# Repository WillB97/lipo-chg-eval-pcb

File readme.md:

# BQ25792/MP2759 LiPo Charger Evaluation Board

[GitHub Pages site](https://willb97.github.io/lipo-chg-eval-pcb/Browse/charger-compare-navigate.html).

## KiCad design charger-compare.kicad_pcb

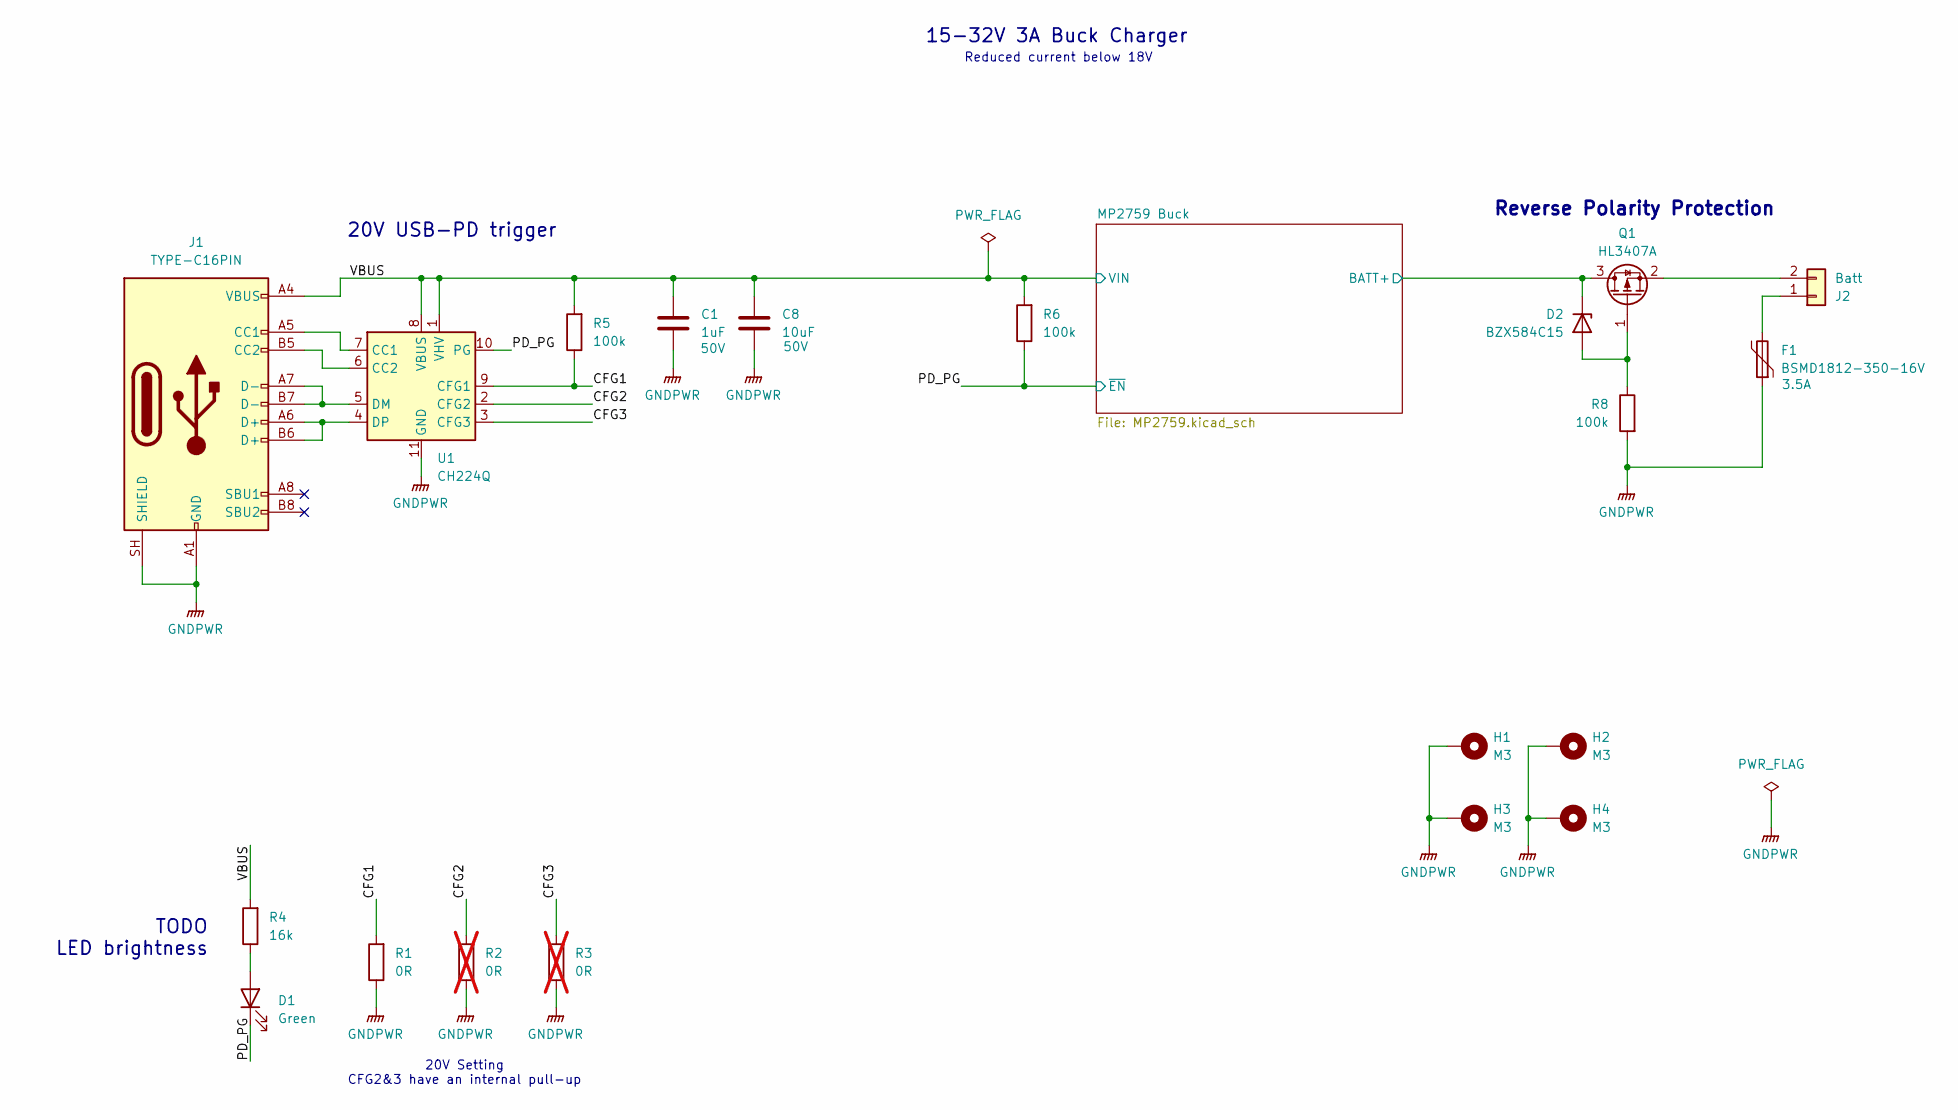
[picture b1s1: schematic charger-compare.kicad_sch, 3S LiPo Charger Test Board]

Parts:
C1: 1uF; C_0603_1608Metric; Voltage 50V; JLC C15849
C8: 10uF; C_0805_2012Metric; Voltage 50V; JLC C440198
D1: Green; LED_0805_2012Metric; JLC C2297
D2: BZX584C15; D_SOD-523; LCSC C19077466
F1: BSMD1812-350-16V; Fuse_1812_4532Metric_Pad1.30x3.40mm_HandSolder; Rating 3.5A; LCSC C5301865
H1, H2, H3, H4: M3; MountingHole_3.2mm_M3_Pad
J1: TYPE-C16PIN; USB_C_Receptacle_Palconn_UTC16-G; LCSC C393939
J2: Batt; AMASS_XT60PW-M_1x02_P7.20mm_Horizontal
Q1: HL3407A; SOT-23; JLC C28646269
R1: 0R; R_0603_1608Metric
R2, R3: 0R; R_0603_1608Metric; not fitted
R4: 16k; R_0402_1005Metric
R5, R6, R8: 100k; R_0402_1005Metric
U1: CH224Q; DFN-10_2x2mm_P0.4mm; LCSC C46061833

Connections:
/CFG1: R1.2, R5.1, U1.9 (CFG1)
/CFG2: R2.2, U1.2 (CFG2)
/CFG3: R3.2, U1.3 (CFG3)
/MP2759 Buck/BATT+: D2.1 (K), Q1.3 (D); also elsewhere on the board
/PD_PG: D1.1 (K), R6.1, U1.10 (PG); also elsewhere on the board
/VBUS: C1.1, C8.1, J1.A4 (VBUS), J1.A9 (VBUS), J1.B4 (VBUS), J1.B9 (VBUS), R4.2, R5.2, R6.2, U1.1 (VHV), U1.8 (VBUS); also elsewhere on the board
GNDPWR: C1.2, C8.2, F1.1, H1.1 (1_1), H2.1 (1_1), H3.1 (1_1), H4.1 (1_1), J1.A1 (GND), J1.A12 (GND), J1.B1 (GND), J1.B12 (GND), J1.SH (SHIELD), R1.1, R2.1, R3.1, R8.2, U1.11 (GND); also elsewhere on the board
unnamed: D1.2 (A), R4.1
unnamed: D2.2 (A), Q1.1 (G), R8.1
unnamed: J1.A5 (CC1), U1.7 (CC1)
unnamed: J1.B5 (CC2), U1.6 (CC2)
unnamed: F1.2, J2.1
unnamed: J2.2, Q1.2 (S)
unnamed: J1.A7 (D-), J1.B7 (D-), U1.5 (DM)
unnamed: J1.A6 (D+), J1.B6 (D+), U1.4 (DP)

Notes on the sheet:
20V USB-PD trigger
Reverse Polarity Protection
TODO LED brightness
20V Setting CFG2&3 have an internal pull-up
Reduced current below 18V
15-32V 3A Buck Charger

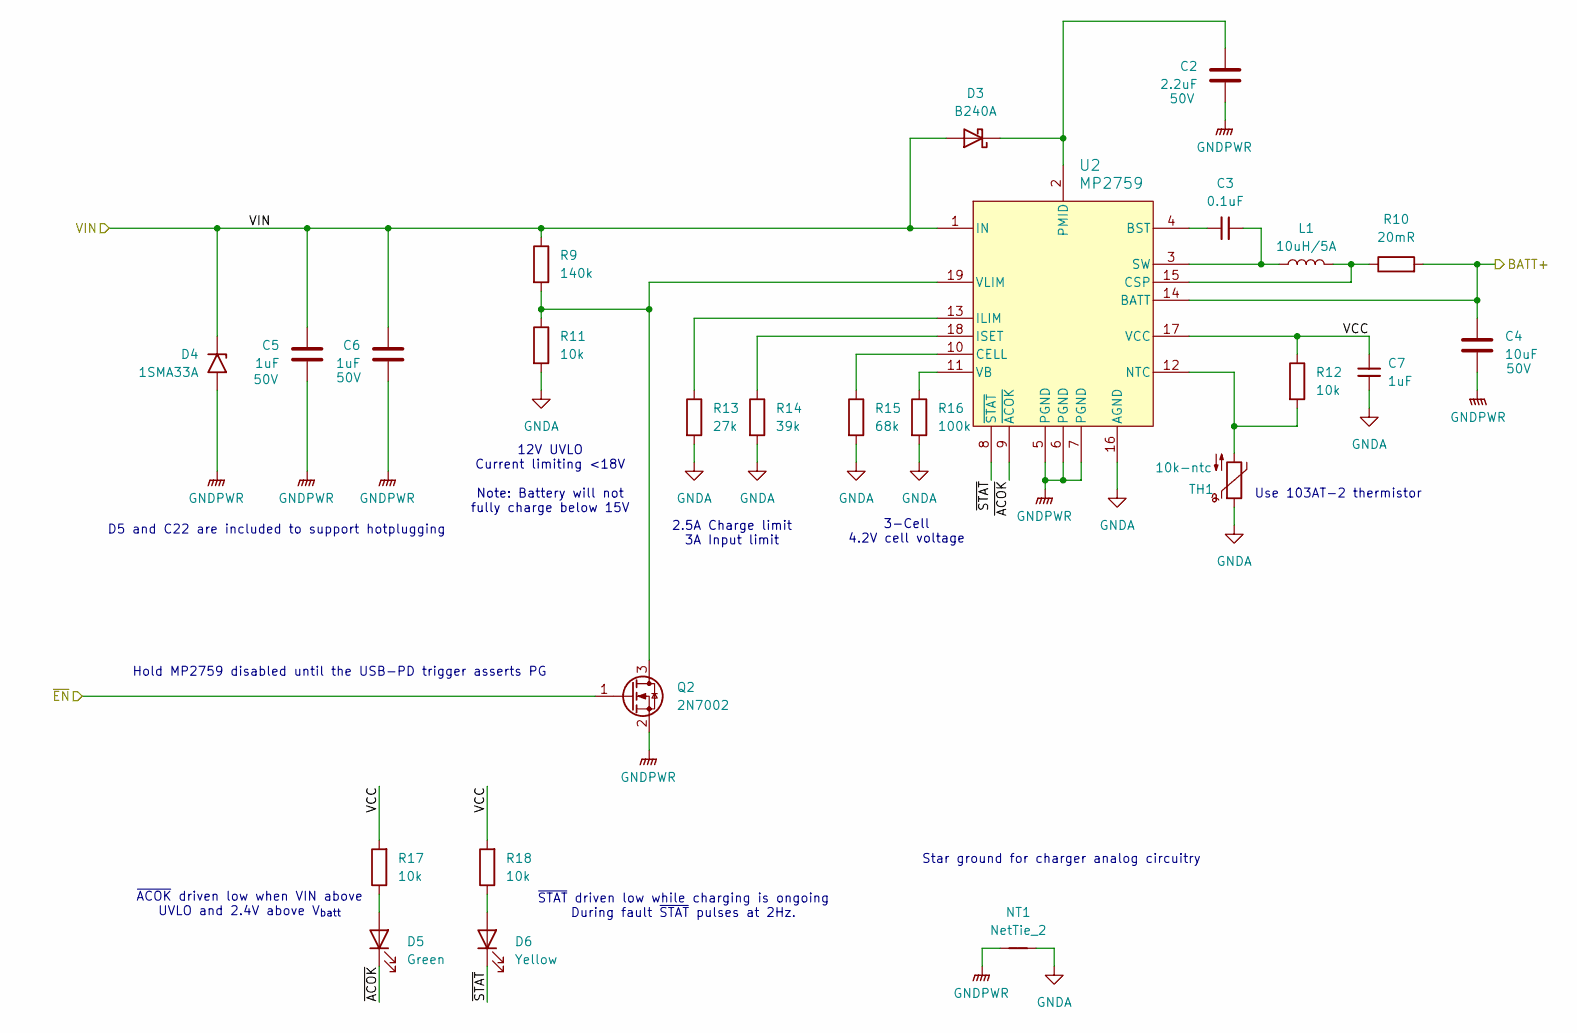
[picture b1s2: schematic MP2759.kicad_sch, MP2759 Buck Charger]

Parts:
C2: 2.2uF; C_0805_2012Metric; Voltage 50V; JLC C377773
C3: 0.1uF; C_0402_1005Metric; Voltage 10V; JLC C307331
C4: 10uF; C_0805_2012Metric; Voltage 50V; JLC C440198
C5, C6: 1uF; C_0603_1608Metric; Voltage 50V; JLC C15849
C7: 1uF; C_0603_1608Metric; Voltage 10V; JLC C15849
D3: B240A; D_SMA; LCSC C39358
D4: 1SMA33A; D_SMA; LCSC C1975650
D5: Green; LED_0805_2012Metric; JLC C2297
D6: Yellow; LED_0805_2012Metric; JLC C2296
L1: 10uH/5A; L_Bourns_SRP7028A_7.3x6.6mm; LCSC C32712974
NT1: NetTie_2; NetTie-2_SMD_Pad0.5mm
Q2: 2N7002; SOT-23
R9: 140k; R_0402_1005Metric; LCSC C2998127
R10: 20mR; R_1206_3216Metric; LCSC C393094
R11, R12, R17, R18: 10k; R_0402_1005Metric
R13: 27k; R_0603_1608Metric
R14: 39k; R_0603_1608Metric
R15: 68k; R_0603_1608Metric
R16: 100k; R_0402_1005Metric
TH1: 10k-ntc; R_0805_2012Metric_Pad1.20x1.40mm_HandSolder
U2: MP2759; QFN-19_MP2759_MNP; LCSC C3682359

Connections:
/MP2759 Buck/BATT+: C4.1, R10.2, U2.14 (BATT); also elsewhere on the board
/MP2759 Buck/VCC: C7.2, R12.1, R17.2, R18.2, U2.17 (VCC)
/MP2759 Buck/~ACOK: D5.1 (K), U2.9 (~ACOK)
/MP2759 Buck/~STAT: D6.1 (K), U2.8 (~STAT)
/PD_PG: Q2.1 (G); also elsewhere on the board
/VBUS: C5.1, C6.1, D3.2 (A), D4.1 (A1), R9.1, U2.1 (IN); also elsewhere on the board
GNDA: C7.1, NT1.2, R11.2, R13.2, R14.2, R15.2, R16.2, TH1.1, U2.16 (AGND)
GNDPWR: C2.2, C4.2, C5.2, C6.2, D4.2 (A2), NT1.1, Q2.2 (S), U2.5 (PGND), U2.6 (PGND), U2.7 (PGND); also elsewhere on the board
unnamed: C2.1, D3.1 (K), U2.2 (PMID)
unnamed: D5.2 (A), R17.1
unnamed: D6.2 (A), R18.1
unnamed: Q2.3 (D), R9.2, R11.1, U2.19 (VLIM)
unnamed: C3.1, U2.4 (BST)
unnamed: R15.1, U2.10 (CELL)
unnamed: L1.2, R10.1, U2.15 (CSP)
unnamed: R13.1, U2.13 (ILIM)
unnamed: R14.1, U2.18 (ISET)
unnamed: R12.2, TH1.2, U2.12 (NTC)
unnamed: C3.2, L1.1, U2.3 (SW)
unnamed: R16.1, U2.11 (VB)

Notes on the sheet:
2.5A Charge limit 3A Input limit
3-Cell 4.2V cell voltage
Hold MP2759 disabled until the USB-PD trigger asserts PG
Use 103AT-2 thermistor
D5 and C22 are included to support hotplugging
~{STAT} driven low while charging is ongoing During fault ~{STAT} pulses at 2Hz.
~{ACOK} driven low when VIN above UVLO and 2.4V above V_{batt}
12V UVLO Current limiting <18V Note: Battery will not fully charge below 15V
Star ground for charger analog circuitry

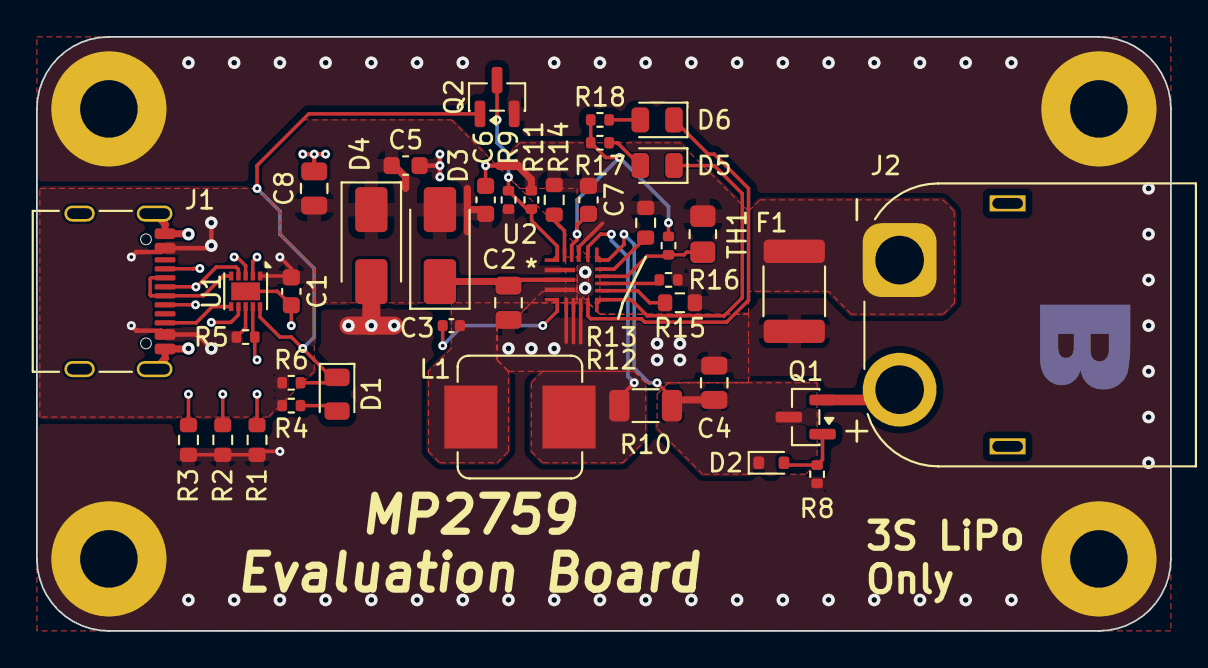
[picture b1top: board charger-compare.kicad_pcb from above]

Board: 4 copper layers, 63.0 x 33.0 mm, 46 parts (1 on the bottom side), 31 nets.

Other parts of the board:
LBL1: WBB

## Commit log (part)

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2025-10-05 Initial design
2025-10-05 Add some CI
2025-10-05 More fixes
2025-10-06 Enable github pages
2025-10-06 Fix reference
2025-10-06 Try older KiBot Add readme
2025-10-06 Put readme in correct location
2025-10-07 Set LED resistors
2025-10-09 Switch to JST-PH connectors Add Sheet titles
2025-10-11 Use custom kibot config
2025-10-11 Try generating kibot configs
2025-10-11 Update gitignore
2025-10-15 Action review feedback
2025-10-16 Add JLC QR code location
2025-10-16 Omit tagconnect for BOM
2025-10-16 Add V1.0 date
